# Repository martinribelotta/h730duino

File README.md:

# H730/733 Duino

Arduino form factor and software compatible board with giant cortex-m7 at 550MHz.

See test firmware [here](https://github.com/martinribelotta/h730duino-firmware)

## Characteristics

- CPU Cortex-M7 at 550MHz.
- 128K/1 MB of internal flash (depending on the MCU version).
- 500 KB of internal RAM.
- 8 MB of external QSPI PSRAM at 133MHz SDR.
- 16/32/128 MB of external QSPI Flash at 133MHz SDR.
- 10/100Mb Ethernet.
- USB 2.0 OTG Type-C with power switch control.
- USB CMSIS-DAP Debugger.
- micro SD Card slot.
- Arduino Due/Mega compatible pin headers (3.3V IO, 5V tolerant on some pins).
- Arduino API compatible (via STM32Duino project).
- Micropython support.
- Protected power inputs with ideal diodes and DC-DC converter

## Capabilities and applications

Some interesting CPU capabilities are listed below:

- Hard real time capable CPU with predictable execution using tightly coupled memory for instruction and data.
- High speed and precision PWM suitable for motor control (BLDC, Stepper, DC).
- High resolution timing measure in capture mode for some pins.
- Arbitrary waveform generation in any GPIO using DMA without CPU intervention.
- High speed DACs suitable to generate analog signals up to 18MHz.
- Tow high speed 12 bits ADC suitable to capture up to 5MSPS in any channel.
- One high speed 16 bits ADC suitable to capture up to 7.5MSPSP
- Internal RAM with multiple block partitions enabling multiple peripheral access at same time without contention.
- External high density RAM up to 8 MB connected across 133MHz QSPI bus accessible in memory mapped mode or block device mode with on the fly encryption/decryption.
- External high density FLASH up to 16 MB connected across 133MHz QSPI bus accessible in memory mapped mode or block device mode with on the fly encryption/decryption.
- Multiplexed parallel memory controller for LCD and TFT access
- LCD interface with 666, 565 and 888 RGB with hsync/vsync and pixel clk (max 150MHz)
- Parallel capture port at 110MHz
- Parallel signal generation at 50MHz

These capabilities enable multiple interesting applications:

- High precision CNC and 3D printing.
- Signal generator and data acquisition system
- Human machine interface enabled terminal with USB, CAN and Ethernet support
- High speed logic analyzer.
- Programmable instrumentation system.
- Network laboratory instrument.

## Layout

 1. MCU STM32H730/733/732
 2. QSPI flash (4/8/16/32MiB)
 3. HyperRAM (8MiB)
 4. 8MHz crystal
 5. 32.768KHz RTC crystal
 6. 5V in regulator
 7. 3.3V main regulator
 8. CMSIS-DAP debugger
 9. Ethernet PHY
 10. USB OTG Full Speed (connected to MCU)
 11. Reset button
 12. User LED
 13. STM32H7 BOOT jumper
 14. MicroSD connector
 15. SWD MCU connector
 16. CMSIS-DAP boot jumper
 17. CMSIS-DAP pogo pins for programming

## Schematics

[Download in PDF format](docs/schematic.pdf)

[Octopart BoM](https://octopart.com/bom-tool/nudLZO8C)

[CSV BoM (octpart compatible)](docs/stm32h7duino-v01.csv)

## License

[MIT License](LICENCE.tx)

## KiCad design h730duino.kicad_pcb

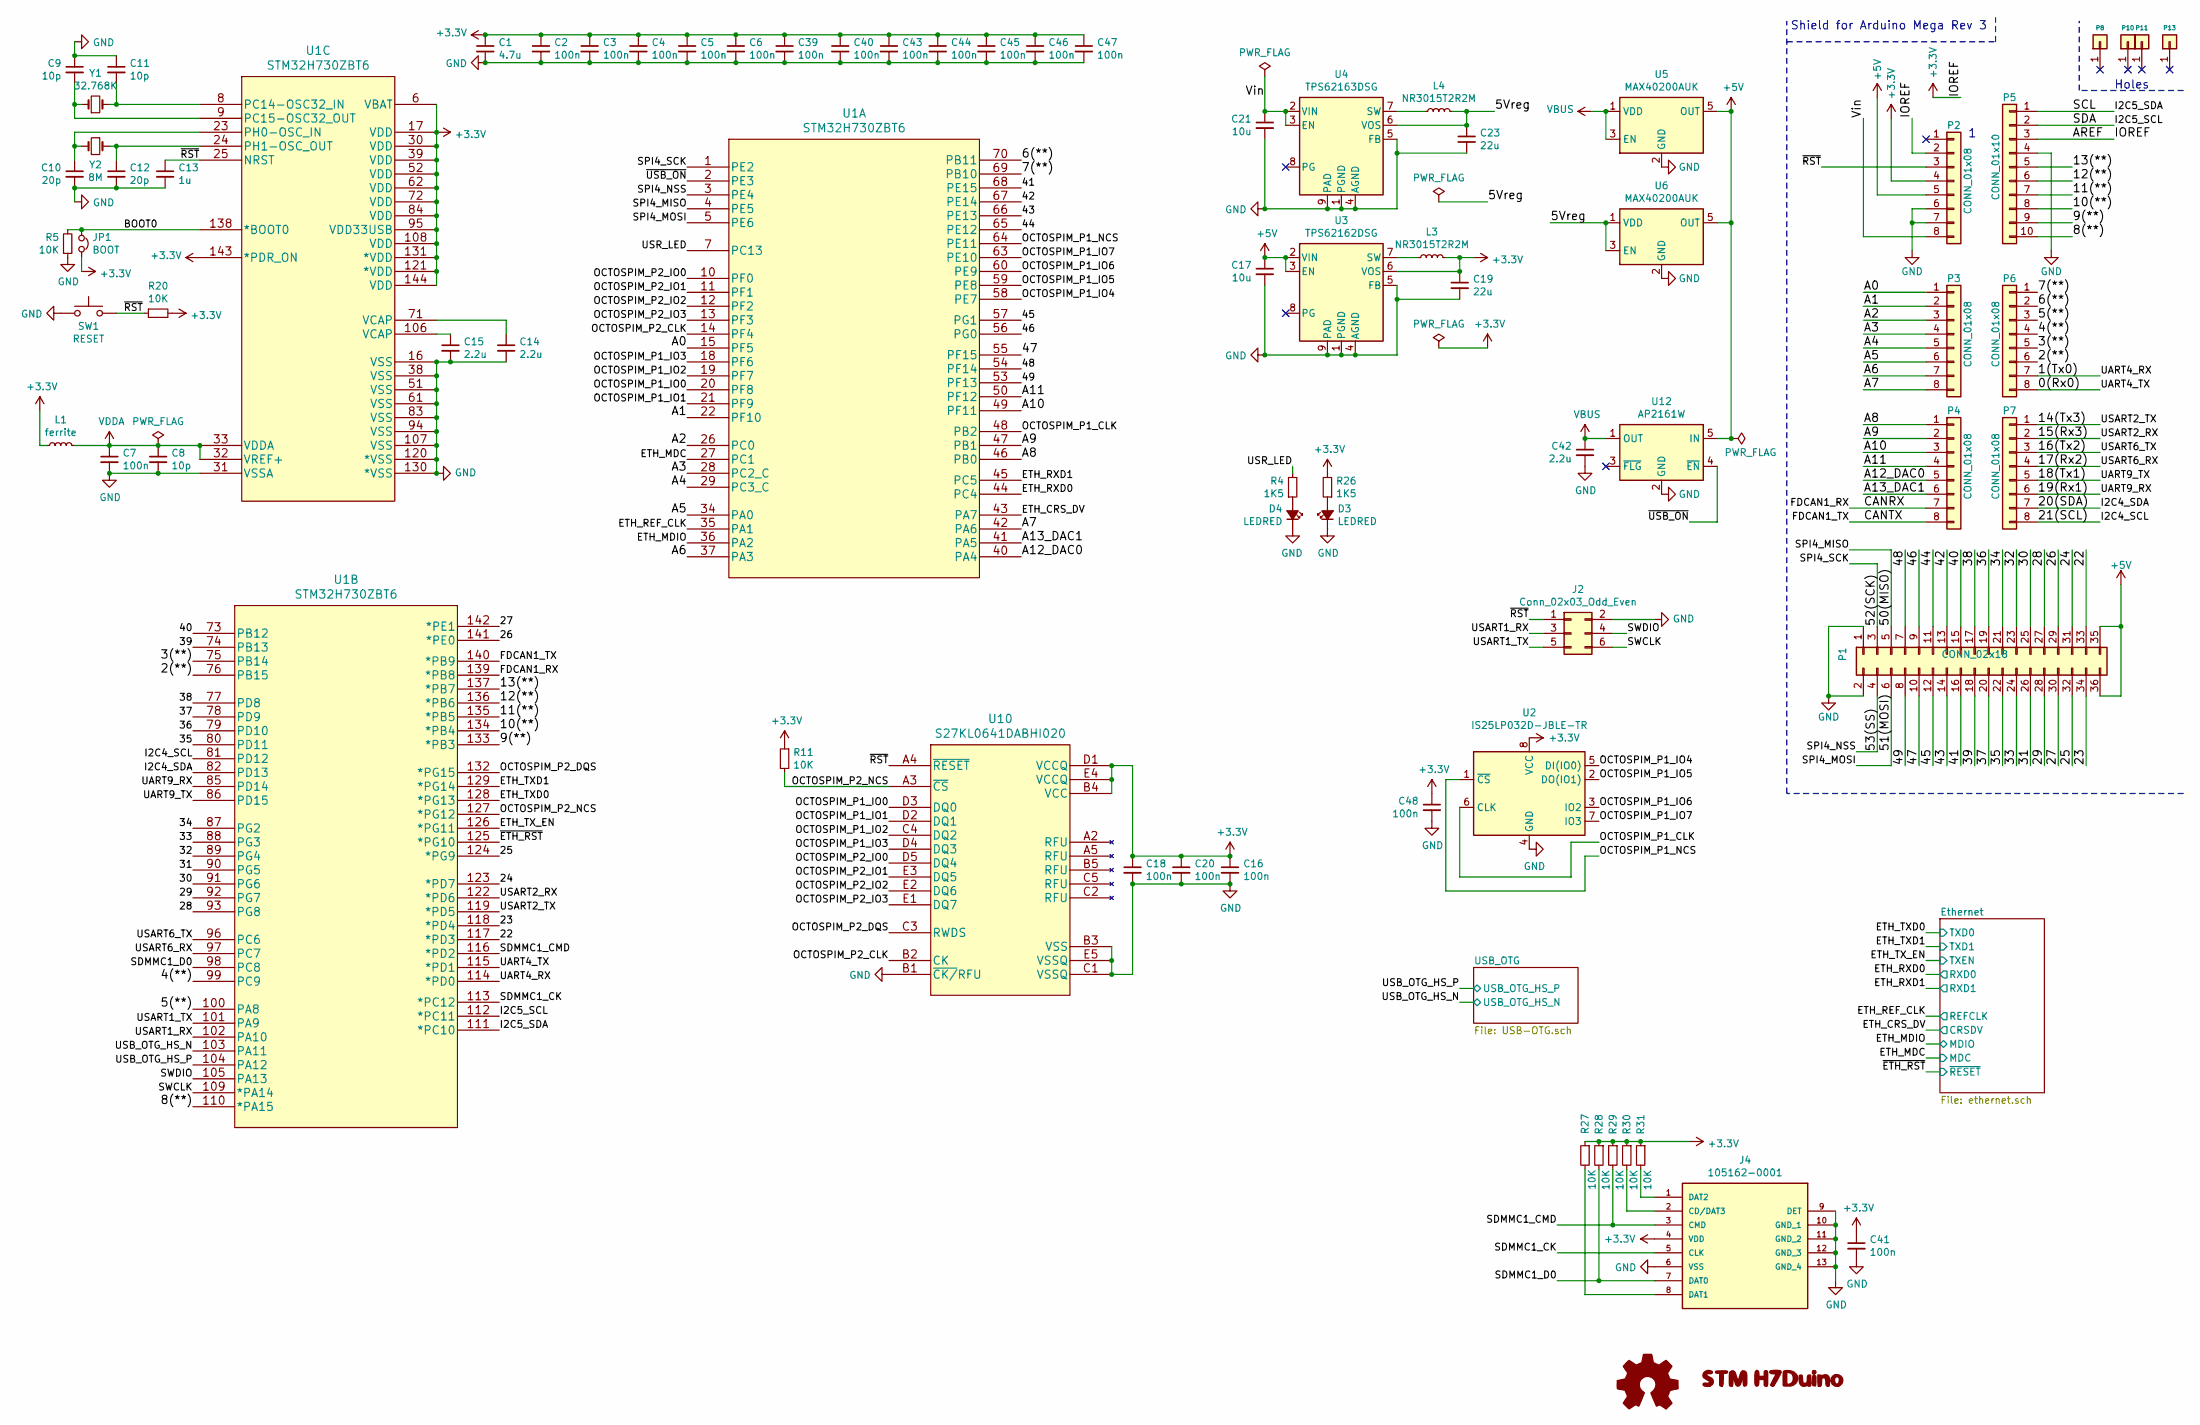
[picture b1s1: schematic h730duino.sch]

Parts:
C1: 4.7u; C_0603_1608Metric; MANUFACTURER_PART_NUMBER CC0603KRX5R5BB475
C2, C3, C4, C5, C6, C7, C16, C18, C20, C39, C40, C41, C43, C44, C45, C46, C47, C48: 100n; C_0603_1608Metric; MANUFACTURER_PART_NUMBER CC0603KRX7R9BB104
C8, C9, C11: 10p; C_0603_1608Metric; MANUFACTURER_PART_NUMBER CC0603JRNPO9BN100
C10, C12: 20p; C_0603_1608Metric; MANUFACTURER_PART_NUMBER CC0603CRNPO9BN1R0
C13: 1u; C_0603_1608Metric; MANUFACTURER_PART_NUMBER CC0603ZRY5V6BB105
C14, C15, C42: 2.2u; C_0603_1608Metric; MANUFACTURER_PART_NUMBER CC0603ZRY5V6BB225
C17, C21: 10u; C_0603_1608Metric; MANUFACTURER_PART_NUMBER 0603ZD106KAT2A
C19, C23: 22u; C_0603_1608Metric; MANUFACTURER_PART_NUMBER GRM188R61A226ME15D
D3, D4: LEDRED; LED_0603_1608Metric; MANUFACTURER_PART_NUMBER LS Q976-NR-1
G1: LOGO; logo
J2: Conn_02x03_Odd_Even; PinHeader_2x03_P2.54mm_Horizontal
J4: 105162-0001; MANUFACTURER_PART_NUMBER 105162-0001; MOUSER_PART_NUMBER 538-105162-0001
JP1: BOOT; PinHeader_1x02_P2.54mm_Vertical
L1: ferrite; L_0603_1608Metric; MANUFACTURER_PART_NUMBER BK1608HS220-T
L3, L4: NR3015T2R2M; L_Taiyo-Yuden_MD-3030; MANUFACTURER_PART_NUMBER NR3015T2R2M
LOGO1: Logo_Open_Hardware_Small; OSHW-Logo_7.5x8mm_SilkScreen
P1: CONN_02x18; Socket_Strip_Arduino_2x18; MANUFACTURER_PART_NUMBER 2044-2X18G00SA
P2, P3, P4, P6, P7: CONN_01x08; Socket_Strip_Arduino_1x08; MANUFACTURER_PART_NUMBER 2044-1X08G00SA
P5: CONN_01x10; Socket_Strip_Arduino_1x10; MANUFACTURER_PART_NUMBER 2044-1X10G00SA
P8, P10, P11, P13: CONN_01X01; Arduino_1pin
R4, R26: 1K5; R_0603_1608Metric; MANUFACTURER_PART_NUMBER RC0603JR-071K5L
R5, R11, R20, R27, R28, R29, R30, R31: 10K; R_0603_1608Metric; MANUFACTURER_PART_NUMBER RC0603FR-0710KL
SW1: RESET; SW_Tactile_SPST_Angled_PTS645Vx39-2LFS; MANUFACTURER_PART_NUMBER PTS645VL58-2 LFS
U1: STM32H730ZBT6; MANUFACTURER_PART_NUMBER STM32H730ZBT6
U2: IS25LP032D-JBLE-TR; SOIC-8_5.23x5.23mm_P1.27mm; MANUFACTURER_PART_NUMBER IS25LP032D-JBLE-TR
U3: TPS62162DSG; WSON-8-1EP_2x2mm_P0.5mm_EP0.9x1.6mm_ThermalVias; MANUFACTURER_PART_NUMBER TPS62162DSG
U4: TPS62163DSG; WSON-8-1EP_2x2mm_P0.5mm_EP0.9x1.6mm_ThermalVias; MANUFACTURER_PART_NUMBER TPS62163DSG
U5, U6: MAX40200AUK; SOT-23-5; MANUFACTURER_PART_NUMBER MAX40200AUK
U10: S27KL0641DABHI020; MANUFACTURER_PART_NUMBER S27KL0641DABHI020
U12: AP2161W; SOT-23-5; MANUFACTURER_PART_NUMBER AP2161W
Y1: 32.768K; Crystal_SMD_3215-2Pin_3.2x1.5mm; MANUFACTURER_PART_NUMBER CM315D32768DZFT
Y2: 8M; Crystal_SMD_5032-2Pin_5.0x3.2mm; MANUFACTURER_PART_NUMBER ABM7-8.000MHZ-D2Y-T

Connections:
+3V3: C1.1, C2.1, C3.1, C4.1, C5.1, C6.1, C16.1, C18.1, C19.1, C20.1, C39.1, C40.1, C41.1, C43.1, C44.1, C45.1, C46.1, C47.1, C48.1, J4.4 (VDD), JP1.1, L1.1, L3.2, P2.2, P2.4, P5.3, R11.1, R20.2, R26.2, R27.1, R28.1, R29.1, R30.1, R31.1, U1.6 (VBAT), U1.17 (VDD), U1.30 (VDD), U1.39 (VDD), U1.52 (VDD), U1.62 (VDD), U1.72 (VDD), U1.84 (VDD), U1.95 (VDD33USB), U1.108 (VDD), U1.121 (*VDD), U1.131 (*VDD), U1.143 (*PDR_ON), U1.144 (VDD), U2.8 (VCC), U3.6 (VOS), U10.B4 (VCC), U10.D1 (VCCQ), U10.E4 (VCCQ); also elsewhere on the board
+5V: C17.1, P1.35, P1.36, P2.5, U3.2 (VIN), U3.3 (EN), U5.5 (OUT), U6.5 (OUT), U12.5 (IN)
/0(Rx0): P6.8, U1.115 (*PD1)
/1(Tx0): P6.7, U1.114 (*PD0)
/2(**): P6.6, U1.76 (PB15)
/3(**): P6.5, U1.75 (PB14)
/4(**): P6.4, U1.99 (PC9)
/5(**): P6.3, U1.100 (PA8)
/5Vreg: C23.1, L4.2, U4.6 (VOS), U6.1 (VDD), U6.3 (EN)
/6(**): P6.2, U1.70 (PB11)
/7(**): P6.1, U1.69 (PB10)
/8(**): P5.10, U1.110 (*PA15)
/9(**): P5.9, U1.133 (*PB3)
/10(**): P5.8, U1.134 (*PB4)
/11(**): P5.7, U1.135 (*PB5)
/12(**): P5.6, U1.136 (*PB6)
/13(**): P5.5, U1.137 (*PB7)
/14(Tx3): P7.1, U1.119 (*PD5)
/15(Rx3): P7.2, U1.122 (*PD6)
/16(Tx2): P7.3, U1.96 (PC6)
/17(Rx2): P7.4, U1.97 (PC7)
/18(Tx1): P7.5, U1.86 (PD15)
/19(Rx1): P7.6, U1.85 (PD14)
/20(SDA): P7.7, U1.82 (PD13)
/21(SCL): P7.8, U1.81 (PD12)
/22: P1.33, U1.117 (*PD3)
/23: P1.34, U1.118 (*PD4)
/24: P1.31, U1.123 (*PD7)
/25: P1.32, U1.124 (*PG9)
/26: P1.29, U1.141 (*PE0)
/27: P1.30, U1.142 (*PE1)
/28: P1.27, U1.93 (PG8)
/29: P1.28, U1.92 (PG7)
/30: P1.25, U1.91 (PG6)
/31: P1.26, U1.90 (PG5)
/32: P1.23, U1.89 (PG4)
/33: P1.24, U1.88 (PG3)
/34: P1.21, U1.87 (PG2)
/35: P1.22, U1.80 (PD11)
/36: P1.19, U1.79 (PD10)
/37: P1.20, U1.78 (PD9)
/38: P1.17, U1.77 (PD8)
/39: P1.18, U1.74 (PB13)
/40: P1.15, U1.73 (PB12)
/41: P1.16, U1.68 (PE15)
/42: P1.13, U1.67 (PE14)
/43: P1.14, U1.66 (PE13)
/44: P1.11, U1.65 (PE12)
/45: P1.12, U1.57 (PG1)
/46: P1.9, U1.56 (PG0)
/47: P1.10, U1.55 (PF15)
/48: P1.7, U1.54 (PF14)
/49: P1.8, U1.53 (PF13)
/50(MISO): P1.5, U1.4 (PE5)
/51(MOSI): P1.6, U1.5 (PE6)
/52(SCK): P1.3, U1.1 (PE2)
/53(SS): P1.4, U1.3 (PE4)
/A0: P3.1, U1.15 (PF5)
/A1: P3.2, U1.22 (PF10)
/A2: P3.3, U1.26 (PC0)
/A3: P3.4, U1.28 (PC2_C)
/A4: P3.5, U1.29 (PC3_C)
/A5: P3.6, U1.34 (PA0)
/A6: P3.7, U1.37 (PA3)
/A7: P3.8, U1.42 (PA6)
/A8: P4.1, U1.46 (PB0)
/A9: P4.2, U1.47 (PB1)
/A10: P4.3, U1.49 (PF11)
/A11: P4.4, U1.50 (PF12)
/A12_DAC0: P4.5, U1.40 (PA4)
/A13_DAC1: P4.6, U1.41 (PA5)
/BOOT0: JP1.2, R5.2, U1.138 (*BOOT0)
/CANRX: P4.7, U1.139 (*PB8)
/CANTX: P4.8, U1.140 (*PB9)
/ETH_CRS_DV: U1.43 (PA7); also elsewhere on the board
/ETH_MDC: U1.27 (PC1); also elsewhere on the board
/ETH_MDIO: U1.36 (PA2); also elsewhere on the board
/ETH_REF_CLK: U1.35 (PA1); also elsewhere on the board
/ETH_RXD0: U1.44 (PC4); also elsewhere on the board
/ETH_RXD1: U1.45 (PC5); also elsewhere on the board
/ETH_TXD0: U1.128 (*PG13); also elsewhere on the board
/ETH_TXD1: U1.129 (*PG14); also elsewhere on the board
/ETH_TX_EN: U1.126 (*PG11); also elsewhere on the board
/I2C5_SCL: P5.2, U1.112 (*PC11)
/I2C5_SDA: P5.1, U1.111 (*PC10)
/OCTOSPIM_P1_CLK: U1.48 (PB2), U2.6 (CLK)
/OCTOSPIM_P1_IO0: U1.20 (PF8), U10.D3 (DQ0)
/OCTOSPIM_P1_IO1: U1.21 (PF9), U10.D2 (DQ1)
/OCTOSPIM_P1_IO2: U1.19 (PF7), U10.C4 (DQ2)
/OCTOSPIM_P1_IO3: U1.18 (PF6), U10.D4 (DQ3)
/OCTOSPIM_P1_IO4: U1.58 (PE7), U2.5 (DI(IO0))
/OCTOSPIM_P1_IO5: U1.59 (PE8), U2.2 (DO(IO1))
/OCTOSPIM_P1_IO6: U1.60 (PE9), U2.3 (IO2)
/OCTOSPIM_P1_IO7: U1.63 (PE10), U2.7 (IO3)
/OCTOSPIM_P1_NCS: U1.64 (PE11), U2.1 (~CS)
/OCTOSPIM_P2_CLK: U1.14 (PF4), U10.B2 (CK)
/OCTOSPIM_P2_DQS: U1.132 (*PG15), U10.C3 (RWDS)
/OCTOSPIM_P2_IO0: U1.10 (PF0), U10.D5 (DQ4)
/OCTOSPIM_P2_IO1: U1.11 (PF1), U10.E3 (DQ5)
/OCTOSPIM_P2_IO2: U1.12 (PF2), U10.E2 (DQ6)
/OCTOSPIM_P2_IO3: U1.13 (PF3), U10.E1 (DQ7)
/OCTOSPIM_P2_NCS: R11.2, U1.127 (*PG12), U10.A3 (~CS)
/SDMMC1_CK: J4.5 (CLK), U1.113 (*PC12)
/SDMMC1_CMD: J4.3 (CMD), R29.2, U1.116 (*PD2)
/SDMMC1_D0: J4.7 (DAT0), R28.2, U1.98 (PC8)
/SWCLK: J2.6, U1.109 (*PA14)
/SWDIO: J2.4, U1.105 (PA13)
/USART1_RX: J2.3, U1.102 (PA10)
/USART1_TX: J2.5, U1.101 (PA9)
/USB_OTG_HS_N: U1.103 (PA11); also elsewhere on the board
/USB_OTG_HS_P: U1.104 (PA12); also elsewhere on the board
/USR_LED: R4.2, U1.7 (PC13)
/Vin: C21.1, P2.8, U4.2 (VIN), U4.3 (EN)
/~ETH_RST: U1.125 (*PG10); also elsewhere on the board
/~RST: C13.1, J2.1, P2.3, R20.1, SW1.1, U1.25 (NRST), U10.A4 (~RESET)
/~USB_ON: U1.2 (PE3), U12.4 (~EN)
GND: C1.2, C2.2, C3.2, C4.2, C5.2, C6.2, C7.2, C8.2, C9.1, C10.2, C11.1, C12.2, C13.2, C14.2, C15.2, C16.2, C17.2, C18.2, C19.2, C20.2, C21.2, C23.2, C39.2, C40.2, C41.2, C42.2, C43.2, C44.2, C45.2, C46.2, C47.2, C48.2, D3.1 (K), D4.1 (K), J2.2, J4.6 (VSS), J4.9 (DET), J4.10 (GND_1), J4.11 (GND_2), J4.12 (GND_3), J4.13 (GND_4), P1.1, P1.2, P2.6, P2.7, P5.4, R5.1, SW1.2, U1.16 (VSS), U1.31 (VSSA), U1.38 (VSS), U1.51 (VSS), U1.61 (VSS), U1.83 (VSS), U1.94 (VSS), U1.107 (VSS), U1.120 (*VSS), U1.130 (*VSS), U2.4 (GND), U3.1 (PGND), U3.4 (AGND), U3.5 (FB), U3.9 (PAD), U4.1 (PGND), U4.4 (AGND), U4.5 (FB), U4.9 (PAD), U5.2 (GND), U6.2 (GND), U10.B1 (~CK/~RFU), U10.B3 (VSS), U10.C1 (VSSQ), U10.E5 (VSSQ), U12.2 (GND); also elsewhere on the board
unnamed: C9.2, U1.9 (PC15-OSC32_OUT), Y1.1
unnamed: C10.1, U1.23 (PH0-OSC_IN), Y2.2
unnamed: C11.2, U1.8 (PC14-OSC32_IN), Y1.2
unnamed: C12.1, U1.24 (PH1-OSC_OUT), Y2.1
unnamed: C14.1, U1.71 (VCAP)
unnamed: C15.1, U1.106 (VCAP)
unnamed: D3.2 (A), R26.1
unnamed: D4.2 (A), R4.1
unnamed: J4.1 (DAT2), R31.2
unnamed: J4.2 (CD/DAT3), R30.2
unnamed: J4.8 (DAT1), R27.2
unnamed: L3.1, U3.7 (SW)
unnamed: L4.1, U4.7 (SW)
VBUS: C42.1, U5.1 (VDD), U5.3 (EN), U12.1 (OUT); also elsewhere on the board
VDDA: C7.1, C8.1, L1.2, U1.32 (VREF+), U1.33 (VDDA)

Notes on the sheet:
Shield for Arduino Mega Rev 3
Holes

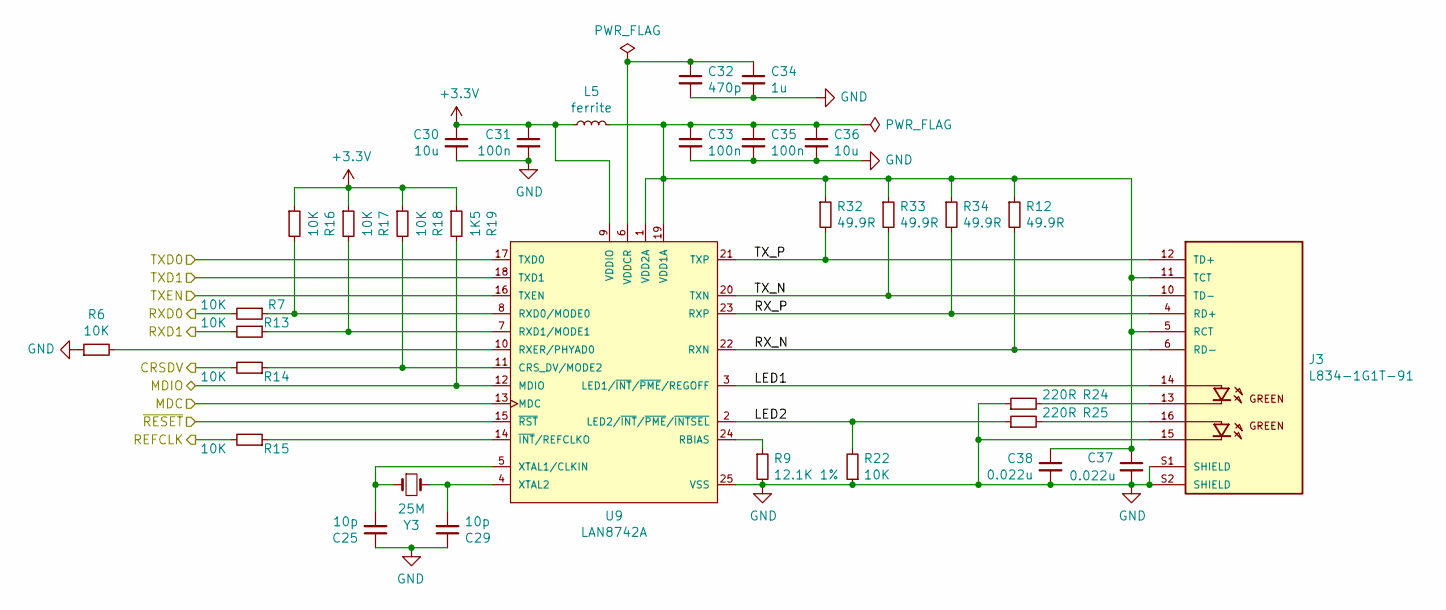
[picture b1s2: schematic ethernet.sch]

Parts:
C25, C29: 10p; C_0603_1608Metric; MANUFACTURER_PART_NUMBER CC0603JRNPO9BN100
C30, C36: 10u; C_0603_1608Metric; MANUFACTURER_PART_NUMBER 0603ZD106KAT2A
C31, C33, C35: 100n; C_0603_1608Metric; MANUFACTURER_PART_NUMBER CC0603KRX7R9BB104
C32: 470p; C_0603_1608Metric; MANUFACTURER_PART_NUMBER 06035C471KAT2A
C34: 1u; C_0603_1608Metric; MANUFACTURER_PART_NUMBER CC0603ZRY5V6BB105
C37, C38: 0.022u; C_0603_1608Metric; MANUFACTURER_PART_NUMBER 06035C223KAT2A
J3: L834-1G1T-91; BEL_L834-1G1T-91; PARTREV C
L5: ferrite; L_0603_1608Metric; MANUFACTURER_PART_NUMBER BK1608HS220-T
R6, R7, R13, R14, R15, R16, R17, R18, R22: 10K; R_0603_1608Metric; MANUFACTURER_PART_NUMBER RC0603FR-0710KL
R9: 12.1K 1%; R_0603_1608Metric; MANUFACTURER_PART_NUMBER RT0603BRD0712K1L
R12, R32, R33, R34: 49.9R; R_0603_1608Metric; MANUFACTURER_PART_NUMBER RC0603FR-0749R9L
R19: 1K5; R_0603_1608Metric; MANUFACTURER_PART_NUMBER RC0603JR-071K5L
R24, R25: 220R; R_0603_1608Metric; MANUFACTURER_PART_NUMBER RC0603JR-07220RL
U9: LAN8742A; Microchip-C04-143B-S4QFN-0-0-MFG; mouser part number 579-LAN8742A-CZ-TR; digikey description IC TRANSCEIVER 1/1 24SQFN
Y3: 25M; Crystal_SMD_5032-2Pin_5.0x3.2mm; MANUFACTURER_PART_NUMBER ABM7-25.000MHZ-D2Y-T

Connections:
+3V3: C30.1, C31.1, L5.1, R16.1, R17.1, R18.1, R19.1, U9.9 (VDDIO); also elsewhere on the board
/ETH_CRS_DV: R14.2; also elsewhere on the board
/ETH_MDC: U9.13 (MDC); also elsewhere on the board
/ETH_MDIO: R19.2, U9.12 (MDIO); also elsewhere on the board
/ETH_REF_CLK: R15.2; also elsewhere on the board
/ETH_RXD0: R7.2; also elsewhere on the board
/ETH_RXD1: R13.2; also elsewhere on the board
/ETH_TXD0: U9.17 (TXD0); also elsewhere on the board
/ETH_TXD1: U9.18 (TXD1); also elsewhere on the board
/ETH_TX_EN: U9.16 (TXEN); also elsewhere on the board
/Ethernet/LED1: J3.14, U9.3 (LED1/~INT~/~PME~/REGOFF)
/Ethernet/LED2: R22.2, R25.1, U9.2 (LED2/~INT~/~PME~/~INTSEL~)
/Ethernet/RX_N: J3.6 (RD-), R12.2, U9.22 (RXN)
/Ethernet/RX_P: J3.4 (RD+), R34.2, U9.23 (RXP)
/Ethernet/TX_N: J3.10 (TD-), R33.2, U9.20 (TXN)
/Ethernet/TX_P: J3.12 (TD+), R32.2, U9.21 (TXP)
/~ETH_RST: U9.15 (~RST~); also elsewhere on the board
GND: C25.1, C29.1, C30.2, C31.2, C32.2, C33.2, C34.2, C35.2, C36.2, C37.2, C38.2, J3.15, J3.S1 (SHIELD), J3.S2 (SHIELD), R6.1, R9.2, R22.1, R24.1, U9.25 (VSS); also elsewhere on the board
unnamed: C25.2, U9.5 (XTAL1/CLKIN), Y3.1
unnamed: C29.2, U9.4 (XTAL2), Y3.2
unnamed: C32.1, C34.1, U9.6 (VDDCR)
unnamed: C33.1, C35.1, C36.1, C37.1, C38.1, J3.5 (RCT), J3.11 (TCT), L5.2, R12.1, R32.1, R33.1, R34.1, U9.1 (VDD2A), U9.19 (VDD1A)
unnamed: J3.13, R24.2
unnamed: J3.16, R25.2
unnamed: R6.2, U9.10 (RXER/PHYAD0)
unnamed: R9.1, U9.24 (RBIAS)
unnamed: R13.1, R17.2, U9.7 (RXD1/MODE1)
unnamed: R14.1, R18.2, U9.11 (CRS_DV/MODE2)
unnamed: R15.1, U9.14 (~INT~/REFCLKO)
unnamed: R7.1, R16.2, U9.8 (RXD0/MODE0)

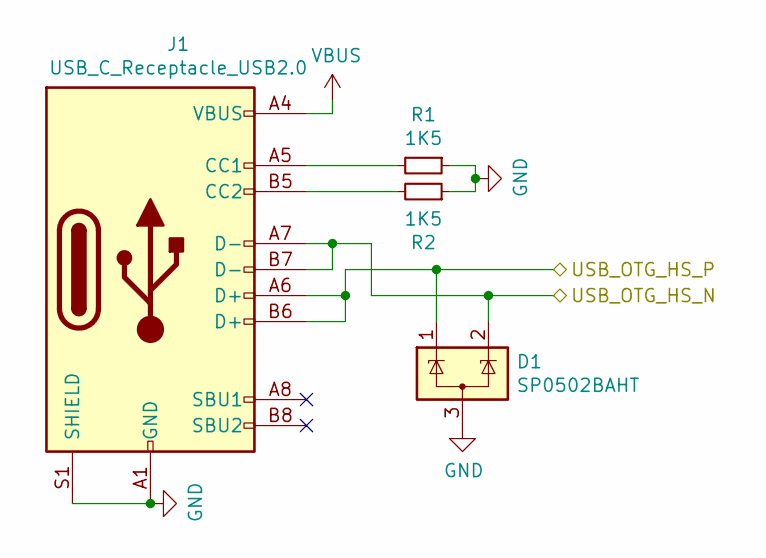
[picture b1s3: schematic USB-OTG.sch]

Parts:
D1: SP0502BAHT; SOT-23; MANUFACTURER_PART_NUMBER SP0502BAHTG
J1: USB_C_Receptacle_USB2.0; USB_C_Receptacle_Amphenol_12401610E4-2A; MANUFACTURER_PART_NUMBER 12401610E4-2A
R1, R2: 1K5; R_0603_1608Metric; MANUFACTURER_PART_NUMBER RC0603JR-071K5L

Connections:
/USB_OTG_HS_N: D1.2 (K), J1.A7 (D-), J1.B7 (D-); also elsewhere on the board
/USB_OTG_HS_P: D1.1 (K), J1.A6 (D+), J1.B6 (D+); also elsewhere on the board
GND: D1.3 (A), J1.A1 (GND), J1.A12 (GND), J1.B1 (GND), J1.B12 (GND), J1.S1 (SHIELD), R1.1, R2.1; also elsewhere on the board
unnamed: J1.A5 (CC1), R1.2
unnamed: J1.B5 (CC2), R2.2
VBUS: J1.A4 (VBUS), J1.A9 (VBUS), J1.B4 (VBUS), J1.B9 (VBUS); also elsewhere on the board

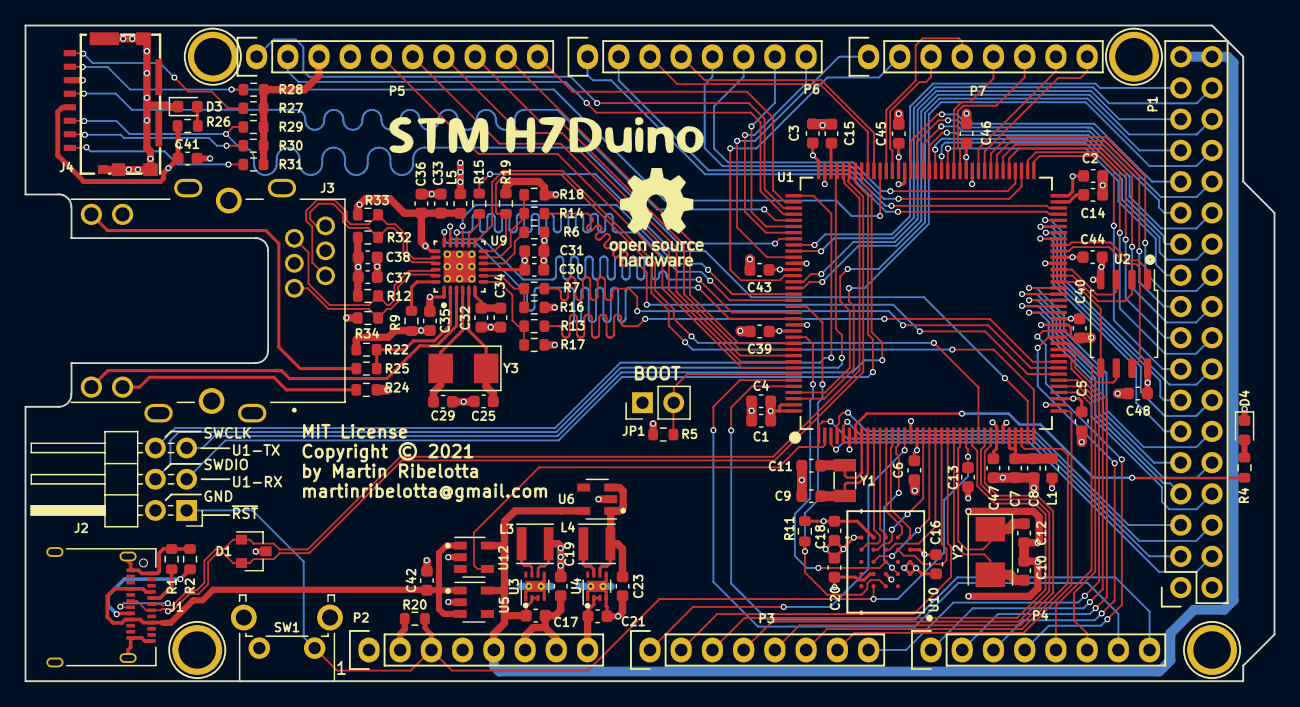
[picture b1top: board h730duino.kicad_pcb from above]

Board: 4 copper layers, 101.6 x 53.3 mm, 111 parts (1 on the bottom side), 152 nets.

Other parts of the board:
QR1: https://github.com/martinribelotta/h730duino; url_qr

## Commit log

2021-02-19 Add gerbers
2021-02-21 Add SWD connector for cortex-m7, SWD poggo pins and boot jumper for cmsis-dap mcu.
2021-02-21 Update README with more info
2021-02-21 Replace non stocked components.
    - Redesign 5V/3.3V using TPS6216xDSGT
    - Use bigger crystal (move to 5031 case)
    - Change some components parts
2021-02-21 Add octopart BOM and update README.md
2021-02-21 Fix REAMDE.md view list and links
2021-02-22 Reorder power supply
2021-03-20 Fix in design:
    - Add r-series to QSPI interfaces
    - Change vCAP from 100n to 2.2u
    - Add pullup to SWCK/DIO and nRST
    - Remove AGND/DGND separation
2021-03-20 Major rework:
    - Split flash/ram in two QSPI iface
    - Flash is connected to QSPI2
    - PSRAM is connected to QSPI1
    - Move QSPI PSRAM near to P1
    - Reorder pins to P1 and P5
    - Reasign I2C5, UART4 to more convenient place
2021-03-21 Improve previous changes:
    - Add pullup resistors to uSD card slot
    - Reroute some signals for more space
    - Check impedance of QSPI/USB signals
    - Match length of uSD signals
2021-03-22 Add new BOM to octopart
    TODO: PSRAM is not recognized by Octopart but is available in LCSC
2021-03-22 Update schemas
2021-03-24 Replace LAN8742 by KSZ8081RND/RNA
2021-03-24 Replace STM32F042 in TSSOP by STM32F04[28] in QFN28
    Others changes:
    - Export gerbers to current status
    - Update schematic export in svg and pdf
    - Update README image
    - Rename `USB OTG` sheet to `USB_OTG`
2021-04-04 Save point
2021-04-05 Change QSPI PSRAM to hyperRAM
    - Replace QSPI PSRAM to HyperBUS version due to erratasheet
    of mcu (cannot write in QSPI mode without DQS and DQS not
    work in 4bit mode)
    - Connect hyperram to QSPI interface 2
    - Move QSPI flash to interface 1
    - Rearrangue pinouts due to new functionality
2021-04-05 Update docs
2021-04-17 Return to lan8742A in ETH PHY
2021-04-18 Prepare for send to PCBWay
2021-04-18 Add BOM for PCBWay
2021-04-18 Add edge cut to gerbers
2021-04-19 Add PCBWay approved gerber files
2021-04-20 Add centroid position files to the gerbers
2021-07-31 Fix 1V8 issue and OSPI pinout
2021-07-31 REally fix HyperRAM connection.
    Additionally:
    - Fix PTH on ETH connector
    - Move USB-C to the left
2021-07-31 Change 1V8 regulator for a more cheap and small part
2021-08-03 Some changes
2021-08-16 Add QR of project URL
2021-08-29 Add firmware link in README

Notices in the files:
h730duino.kicad_pcb:
Copyright © 2021
parts and their libraries:
Copyright 2016 Accelerated Designs. All rights reserved.
